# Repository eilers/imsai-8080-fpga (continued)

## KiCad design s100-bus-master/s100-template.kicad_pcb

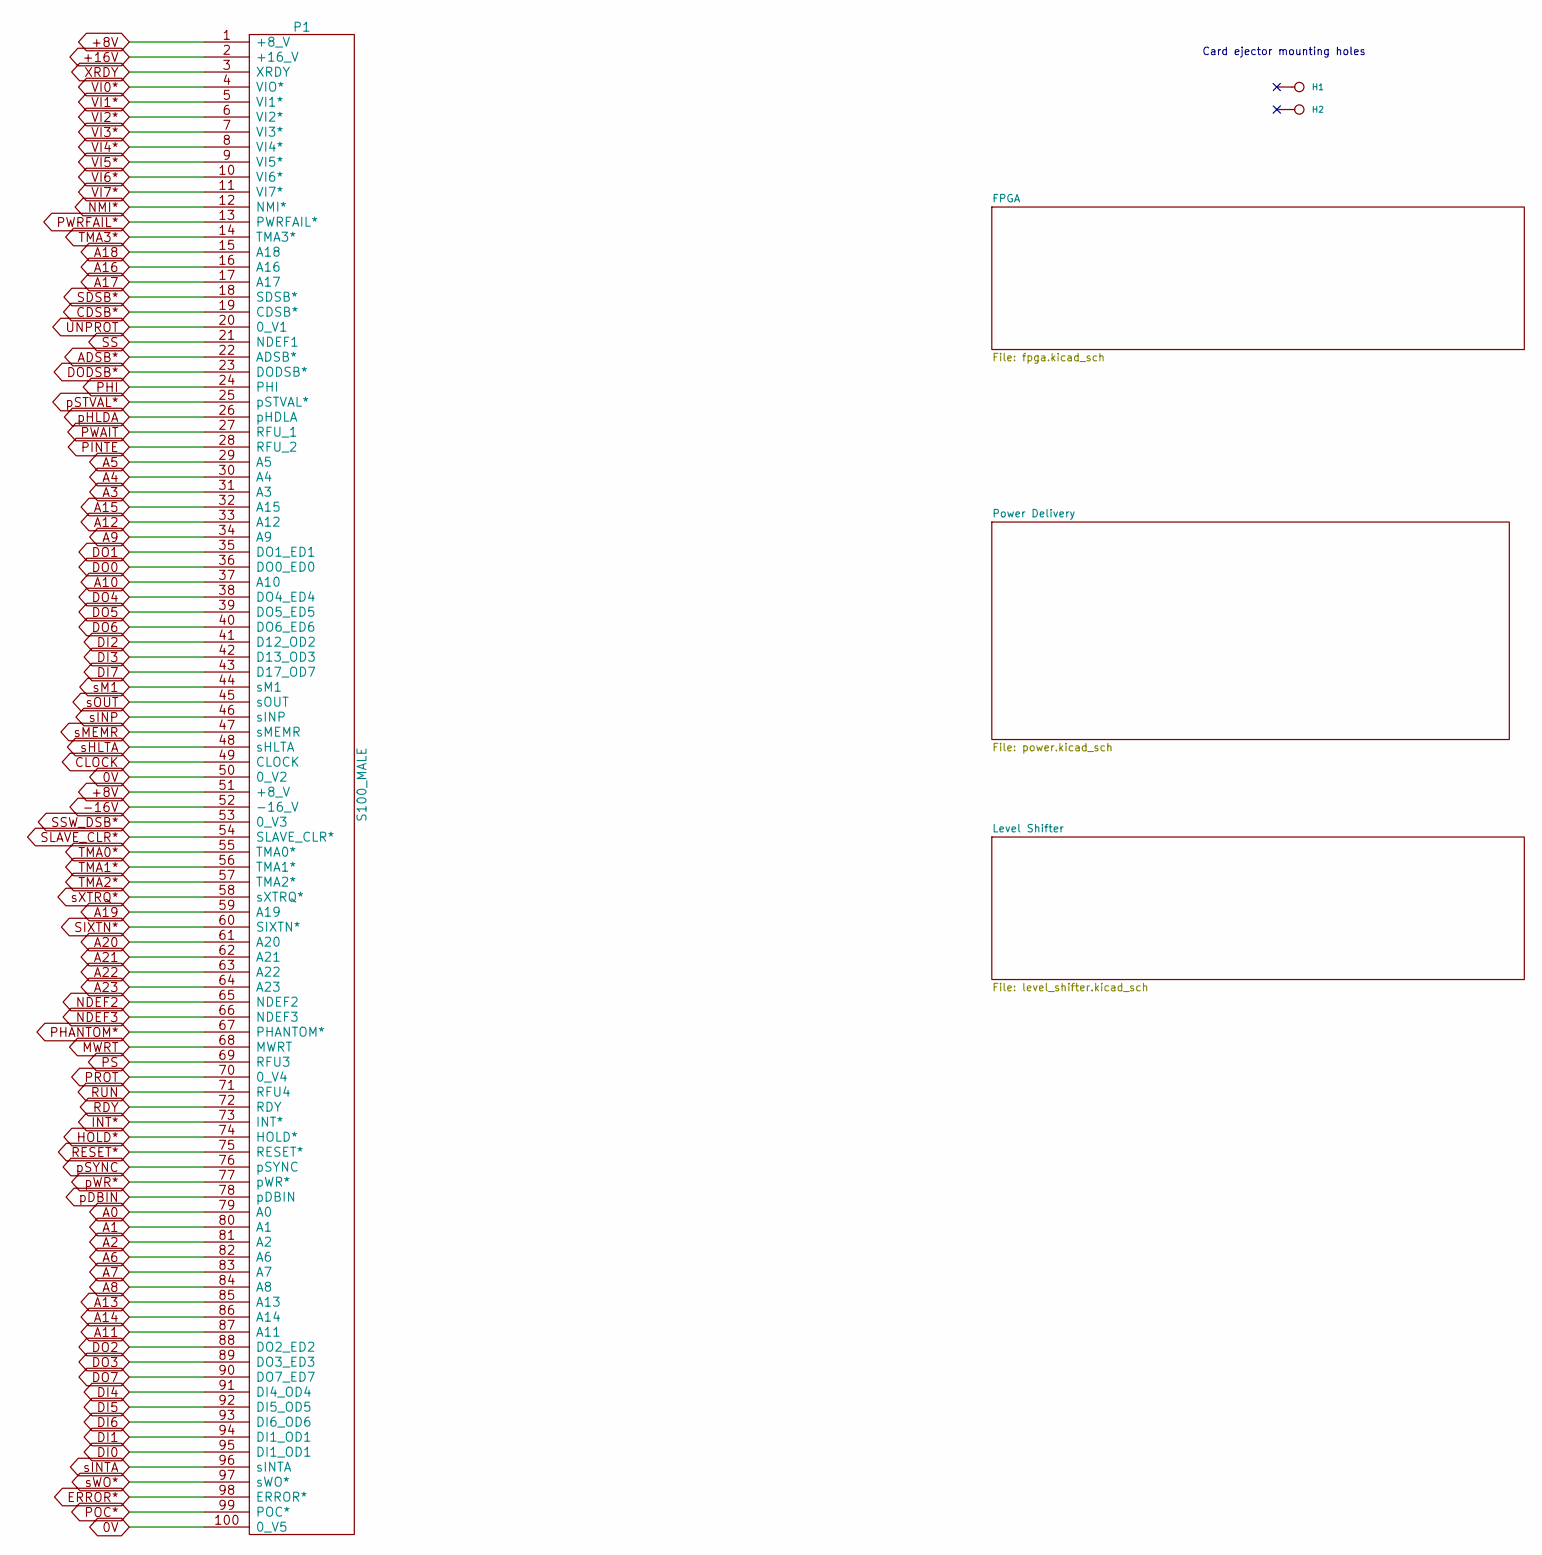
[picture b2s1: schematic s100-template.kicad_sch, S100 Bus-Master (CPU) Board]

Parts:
H1, H2: Ejector; s100-ejector
P1: S100_MALE; s100-edge-connector-male

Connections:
0V: P1.50 (0_V2), P1.100 (0_V5); also elsewhere on the board
+8V: P1.1 (+8_V), P1.51 (+8_V); also elsewhere on the board
+16V: P1.2 (+16_V)
-16V: P1.52 (-16_V)
A0: P1.79 (A0); also elsewhere on the board
A1: P1.80 (A1); also elsewhere on the board
A2: P1.81 (A2); also elsewhere on the board
A3: P1.31 (A3); also elsewhere on the board
A4: P1.30 (A4); also elsewhere on the board
A5: P1.29 (A5); also elsewhere on the board
A6: P1.82 (A6); also elsewhere on the board
A7: P1.83 (A7); also elsewhere on the board
A8: P1.84 (A8); also elsewhere on the board
A9: P1.34 (A9); also elsewhere on the board
A10: P1.37 (A10); also elsewhere on the board
A11: P1.87 (A11); also elsewhere on the board
A12: P1.33 (A12); also elsewhere on the board
A13: P1.85 (A13); also elsewhere on the board
A14: P1.86 (A14); also elsewhere on the board
A15: P1.32 (A15); also elsewhere on the board
A16: P1.16 (A16); also elsewhere on the board
A17: P1.17 (A17); also elsewhere on the board
A18: P1.15 (A18); also elsewhere on the board
A19: P1.59 (A19); also elsewhere on the board
A20: P1.61 (A20); also elsewhere on the board
A21: P1.62 (A21); also elsewhere on the board
A22: P1.63 (A22); also elsewhere on the board
A23: P1.64 (A23); also elsewhere on the board
ADSB*: P1.22 (ADSB*); also elsewhere on the board
CDSB*: P1.19 (CDSB*); also elsewhere on the board
CLOCK: P1.49 (CLOCK); also elsewhere on the board
DI0: P1.95 (DI1_OD1); also elsewhere on the board
DI1: P1.94 (DI1_OD1); also elsewhere on the board
DI2: P1.41 (D12_OD2); also elsewhere on the board
DI3: P1.42 (D13_OD3); also elsewhere on the board
DI4: P1.91 (DI4_OD4); also elsewhere on the board
DI5: P1.92 (DI5_OD5); also elsewhere on the board
DI6: P1.93 (DI6_OD6); also elsewhere on the board
DI7: P1.43 (D17_OD7); also elsewhere on the board
DO0: P1.36 (DO0_ED0); also elsewhere on the board
DO1: P1.35 (DO1_ED1); also elsewhere on the board
DO2: P1.88 (DO2_ED2); also elsewhere on the board
DO3: P1.89 (DO3_ED3); also elsewhere on the board
DO4: P1.38 (DO4_ED4); also elsewhere on the board
DO5: P1.39 (DO5_ED5); also elsewhere on the board
DO6: P1.40 (DO6_ED6); also elsewhere on the board
DO7: P1.90 (DO7_ED7); also elsewhere on the board
DODSB*: P1.23 (DODSB*); also elsewhere on the board
ERROR*: P1.98 (ERROR*); also elsewhere on the board
HOLD*: P1.74 (HOLD*); also elsewhere on the board
INT*: P1.73 (INT*); also elsewhere on the board
MWRT: P1.68 (MWRT); also elsewhere on the board
NDEF2: P1.65 (NDEF2)
NDEF3: P1.66 (NDEF3)
NMI*: P1.12 (NMI*); also elsewhere on the board
PHANTOM*: P1.67 (PHANTOM*); also elsewhere on the board
PHI: P1.24 (PHI); also elsewhere on the board
PINTE: P1.28 (RFU_2); also elsewhere on the board
POC*: P1.99 (POC*); also elsewhere on the board
PROT: P1.70 (0_V4)
PS: P1.69 (RFU3)
PWAIT: P1.27 (RFU_1); also elsewhere on the board
PWRFAIL*: P1.13 (PWRFAIL*); also elsewhere on the board
RDY: P1.72 (RDY); also elsewhere on the board
RESET*: P1.75 (RESET*); also elsewhere on the board
RUN: P1.71 (RFU4)
SDSB*: P1.18 (SDSB*); also elsewhere on the board
SIXTN*: P1.60 (SIXTN*)
SLAVE_CLR*: P1.54 (SLAVE_CLR*); also elsewhere on the board
SS: P1.21 (NDEF1)
SSW_DSB*: P1.53 (0_V3); also elsewhere on the board
TMA0*: P1.55 (TMA0*); also elsewhere on the board
TMA1*: P1.56 (TMA1*); also elsewhere on the board
TMA2*: P1.57 (TMA2*); also elsewhere on the board
TMA3*: P1.14 (TMA3*); also elsewhere on the board
UNPROT: P1.20 (0_V1)
VI0*: P1.4 (VIO*); also elsewhere on the board
VI1*: P1.5 (VI1*); also elsewhere on the board
VI2*: P1.6 (VI2*); also elsewhere on the board
VI3*: P1.7 (VI3*); also elsewhere on the board
VI4*: P1.8 (VI4*); also elsewhere on the board
VI5*: P1.9 (VI5*); also elsewhere on the board
VI6*: P1.10 (VI6*); also elsewhere on the board
VI7*: P1.11 (VI7*); also elsewhere on the board
XRDY: P1.3 (XRDY); also elsewhere on the board
pDBIN: P1.78 (pDBIN); also elsewhere on the board
pHLDA: P1.26 (pHDLA); also elsewhere on the board
pSTVAL*: P1.25 (pSTVAL*); also elsewhere on the board
pSYNC: P1.76 (pSYNC); also elsewhere on the board
pWR*: P1.77 (pWR*); also elsewhere on the board
sHLTA: P1.48 (sHLTA); also elsewhere on the board
sINP: P1.46 (sINP); also elsewhere on the board
sINTA: P1.96 (sINTA); also elsewhere on the board
sM1: P1.44 (sM1); also elsewhere on the board
sMEMR: P1.47 (sMEMR); also elsewhere on the board
sOUT: P1.45 (sOUT); also elsewhere on the board
sWO*: P1.97 (sWO*); also elsewhere on the board
sXTRQ*: P1.58 (sXTRQ*)

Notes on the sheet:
Card ejector mounting holes
